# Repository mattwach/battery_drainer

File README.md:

# battery_drainer

This project describes hardware to safely discharge batteries to a user-chosen
level.

# Why?

Before I started flying RC models (many years ago), the concept of managing
batteries was off my radar.  While in the hobby, it became clear that proper
management makes a big difference in how long batteries last and how much power
they will deliver.

Storing lithium ion batteries fully-charged or fully-drained causes them to
degrade permanently.  It's much better to store them in a half-charged state.

Since lithium batteries are used basically everywhere (phones, tools, laptops,
    cars, on and on), being aware of these concepts can help you keep more of
your devices running longer and more healthy.

Many non-lithium batteries have "memory effects" and can benefit from a deep
discharge now and then.  See your particular battery type for details on how to
maintain/restore it.

Other applications for discharging include testing battery capacity and
preparing it for disposal.

# Caution

Following anything written in this document is at-your-own risk.

Batteries are energy storage devices and thus carry an inherent risk.  If you
are not familiar with the battery type you are working with, take a few moments to
educate yourself on recommended handling practices.

When working with an untested unit or new batteries, I suggest extra caution.
For example doing initial testing outside on concrete or in a fire pit.

This design incorporates a protection fuse.  I recommend using the
*smallest-sized fuse* that meets your requirements.  If anything goes wrong
with the firmware, a hardware component, or the hardware build, the fuse will
limit the maximum current that can flow.  Starting with a small fuse and
upgrading it later could be a good verification strategy.

# Pre-existing Market Solutions

If you look up "LIPO Battery Discharger" on Amazon or similar, you will find a
variety of products.  These might work for you but note that the project I am
describing has some advantages over what you can buy:

1. Higher maximum power.  The unit I built is running great at 350W.  The components
   I chose are speced to 460W and 30A.  Since you are building it yourself,
   you can choose a transistor/cooling combo that supports the power dissipation
   you need.
2. Support for "safe" multiboards.  My project has a diode-protected multiboard
   that allows you to safely plug in multiple batteries that are at different 
   discharge levels. This protection requires the discharger account for the 
   voltage drop across the protection diodes, which commercial charges do not
   typically do.
3. Support of 1S packs.  Many chargers have a 2S minimum.
4. Lots of customization.  My project lets you customize voltages and
   create special profiles.  For example, I have one that takes packs down to
   4V/Cell, which is useful for packs that I want ready-to-use in worklights and tools.
5. Detailed status.  The OLED of this project gives lots of information
   during the discharge which can help you guage the health of the pack.
6. Support for more battery types than just LIPO, due to the extensive 
   customization ability.

# Using

## User Interface

The unit has four UI buttons: On, Off, Select and OK.

When the device is initially powered up, it will display the current voltage,
cell count and the target voltage.  It also shows a scrollable list of
profiles to choose from:

The user chooses a profile with "Select" and presses "OK" to start discharging.
During discharge, the following status information is displayed (the ghosting
in the image is because the unit was actively updating during the photo):

Information shown includes:

* Time running
* Number of mAH discharged so far
* Battery voltage and cell count
* Target voltage
* Discharge Current
* Power (Voltage * Current)
* Temperature
* FET power level %
* Fan power level %

If the FET power level is limited < 100%, then the parameter that is limiting
the power is highlighted as inverse text.  In the example above, this limit is
overall power draw.  A lower-cell-count battery might hit the max current
instead.  A small battery might be limited by voltage sag.  A hot day might
introduce a temperature limit.  All limits are user configurable - but you'll
need to be aware of what your built hardware can handle and test higher limits
with due caution.

When the discharge is complete, the unit will show some stats for a configurable
amount of time before automatically shutting down.  Here is an example:

After shutdown, the unit takes very little power (a few microamps) to avoid
further unintended drainage of smaller packs.

## Configuration

Profiles can be edited by connecting a computer to the unit via USB and starting
a terminal program.  On my Linux laptop, I used:

    minicom -b 115200 -P /dev/ttyUSB0

Refer to the [dedicated configuration guide](configuration.md) for details
about how to configure settings, calibrate the device and create/edit profiles.

# Building

## Parts list

To see the parts list, open up the schematic in KiCad and look at the "Symbol
Fields Table".  It looks like a spreadsheet icon in the UI.  Here you will find
a list of parts and links for building an order.  Here is a snapshot of what
the list looked like at some point:

## Schematic Overview

Note that the images below are a snapshot of the schematic and not fully
up-tp-date.  See the KiCad original for the latest design.

Here is the complete design (click to expand):

Here is an early Falstad simulation that gives a basic idea of how the circuit
works:

https://tinyurl.com/2qg4xwyj

There is much going on here.  The sections below break down and explain one
subcircuit at a time.

### Power Dissipation

[Falstad model](https://tinyurl.com/28p9fv3n)

This is a set of 4 P-Channel MOSFETs connected in parallel:

More or less *could* also work.

**Note** The schematic shows four PFETs in parallel.  The unit *I actually
built* uses a single high-power FET instead.  I think that four PFETs would
still work but have not confirmed it.  The main risk of using 4 is that they
will be unevenly loaded to the point where one of them is damaged.  I do
believe that they will be unevenly loaded at lower currents but not after the
current ramps up enough to matter.  Again, I have not confirmed this.  Using a
single high-power FET is my recommendation if you want to play it safer.

The FETs in this design are (unusually) run in their "Ohmic" region which
is controlled by the gate-to-source voltage (Vgs) as exampled in the FQP27P06
datasheet graph below:

### Vgs Control

[Falstad model](https://tinyurl.com/2bj46fut)

To achieve the target Vgs for the FETs, we the following circuit:

The main element here is the 10u capacitor on the right side of the image.
The voltage across this capacitor is the gate voltage that
each FET will see.

Filling the capacitor is the 5k resistor, R16.  If only this resistor and the
capacitor existed, then the RC constant would be 5000 * 10e-6 = 50ms.  When the
capacitor is sufficiently charged, the FETs will be turned off.

The two transistors (Q6, Q9) are used to drain the capacitor.  The one on the
left is a "slow" drain and the one on the right is a "fast" drain.  The size of
the resistors (R17 and R20) determines the drain speed.  A microcontroller
feeds in a PWM to open/close the transistor.  The duty cycle of this PWM
signal determines how much current is pulled on average and the frequency
of this PWM signal determines how smooth/stable the voltage will be.

The reason for two drains (verses one) is to support a larger voltage
range.  At lower voltages (4V), the FAST drain circuit is needed
to get the Vgs lower than the SLOW drain can achieve.  For higher voltages
(25V), the SLOW drain provides better control resolution.  Depending on the
FET you go with and voltage range you want to support, a single drain
may work fine.

In the power-on state, we can assume that SLOW and FAST are not driven at all
(high Z).  In this state the two 50k pulldown resistors (R14, R18) turn off Q6
and Q9 causing the capacitor to fill up and turn off the main power FETs.

The 100K pull down resistor (R25) slowly drains the capacitor so that it at a known
voltage (0V) when the unit is unplugged and idle.

## Inrush protection

[Falstad model](https://tinyurl.com/2y8c54c8)

On initial battery plug-in, the 100ms or so it takes the capacitor (C4) to
charge via R16 could allow a high current to pass through the FETs for that
time period.  This is mitigated by the following inrush protection circuitry:

Fully understanding this block will require studying the full schematic.  A
partial understand can be gained from the image above and the Falstad model.  We
basically have another way to fill the capacitor C4 which is "enabled" when the
battery is plugged in but the user has not pressed the power button yet.  The
way this works is that the source of the FET Q5 is connected to the battery
and the small 10 ohm R13 allows for a rapid fill.  R8 is connected to the
microcontroller power and is thus grounded on plug-in, turning "on" the
FET.

When the user powers on the device (after the battery is plugged in), there is
voltage near-battery going to R8 which turns off the FET and cuts off R13.

### Current Sense 

[Falstad model](https://tinyurl.com/253e6aln)

One of the four ways the microcontroller decides where to set Vgs is by
monitoring the current flowing through the FETs  (the other three are voltage,
power, and temperature).  An ADC within the microcontroller measures the voltage
across the resistors (R22-R24) then uses Ohm's law (I = V/R) to determine the
current.

Resistor values were chosen for a full 3V swing at 30A of current, this allows
us to use the full 12-bits of ADC resolution for good accuracy.  The downside
is that 3V * 30A = 90W, which is a lot for a resistor to dissipate.  To support
this, I chose 3 35W 0.4 ohm resistors connected in parallel for a total dissipation
capability of ~100W and an equivalent resistance of 0.133 ohm.  Potentially
wasting this much power on a current measurement would normally be frowned upon but
in this application it's actually helping take some load off the main power FET.

A Zener diode (U5) is used to protect the ADC of the microcontroller in the
event that the divided voltage is too high (> 3V).  This is a protection
feature that serves no function under "normal" operating conditions.

### Protection Fuse

We also have a protection fuse to help protect against software bugs or other
unexpected problems.  More protection would be offered if the fuse were right at
the battery input but this would introduce a further temperature-dependent
voltage drop that would throw off the voltage measurement.  The "unprotected"
components are the digital logic which should be low current draw barring a
physical issue with the board (< 100 mA)

### Voltage Sense

[Falstad model](https://tinyurl.com/2aavu5hb)

The microcontroller monitors the overall battery voltage to determine a sag
value and to determine when the drain process is completed.

The circuit is a simple voltage divider with a capacitor to help stabilize the
reading.

Sag is determined by periodically turning off the FETs (say for one second every
15 seconds) and measuring the "unloaded" voltage of the pack.  This can then be
used a reference value to determine the sag.

The voltage at R9 is not exactly the battery voltage as it has to pass through a
a diode and FET.  The software provides a calibration value to account for this
drop.

### Temperature Sense

A temperature sensor is placed against the heatsink and as-close-as-possible to
the FET to monitor the FET temperature.  This feedback can be used to control a
cooling fan (described below) and, if this is inadequate, reduce the current draw.

### Power cutoff

[Falstad model](https://tinyurl.com/22wuu5mp)

The battery drainer is designed to draw nearly zero power (outside of parasitic
losses) when it is off, including after the discharging has completed.  Thus the
user can leave the unit unattended (assuming the needed precautions have been
taken) without concern of parasitic drain.

This is implemented with the following circuit:

The Q2 FET is key.  It determines if the microcontroller gets any power.
Q2 is off by default, turned off by R2.  There are two ways to turn it on:

1. If the user presses SW5
2. If the microcontroller activates Q1 via "EN".  The microcontroller does
   this as soon as it can (in a split second) and holds it high until the
   microcontroller decides that it is time to power down OR the user presses
   the "OFF" button which forces Q2 off.

### ADC reference

When using an ADC, one can typically choose from several different sources for
the calibration with the internally-generated 3.3V source as the most
convenient.  The downside of choosing this source is mediocre accuracy.

This design uses the alternate `ADC_VREF` input with a `LM4040` voltage reference
to allow for more accurate measurements.

### OLED connection

The design breaks out an I2C 4 pin header that is typical for an I2C OLED.  A
128x64 design is the intended unit but anything that supports I2C could be
supported with appropriate firmware modifications.

### Fan connection

The battery drainer effectively converts battery energy to heat, thus you'll need
a cooling strategy to avoid overheating and damaging the discharge circuit.
Like cooling other devices such as CPUs and GPUs, a passive solution is
sometimes adequate and an active solution is often needed.

The circuitry below supports a PWM-based fan controller.

The circuit is just a 12V linear regulator with supporting capacitors.  The
connections support "PWM" style PC case fans which generally accept a 25Khz
PWM signal on pin 4.

A flyback diode is needed when powering generic motors but is unlikely to be
needed here as PWM-controlled motors usually already have one in the motor
control circuit.  You can add one for peace-of-mind if you choose.

### PI Pico Microcontroller

As is typical, a microcontroller orchestrates the operation.  Here I chose a PI
Pico because it is inexpensive and quite capable.  It's main downside is the
lack of a low-power sleep mode, but the Power cutoff circuit explained above
compensates for this shortcoming.

A little bit on the tasks the Pico must attend to:

1. When the unit is powered-up, the Pico must raise the EN pin to keep the power  
   active.  It must lower the EN pin when it is time to shutdown.
2. It controls the dissipation rate of the main FETs via PWM signals on the SLOW 
   and FAST pins.
3. It measures current by ADC decoding the voltage at the CUR pin.
4. It measures the battery voltage via an ADC.
5. It provides an output display via SDA and SCL
6. It controls the fan speed (if present) via the FAN pin.
7. It monitors the buttons Select and OK buttons.

## PCB Layout

The PCB layout is above.  Some notes on the layout:

* The dimensions of the board are 122 x 88 mm (4.8 x 3.5 inches)
* Power FETs and resistors are aligned so that a single (large) heatsink can service all of them
* Large traces are used in the higher current areas.
* Large vias are used to try and distribute current and reduce hotspots. 

I went with thicker 2oz copper when manufacturing this board to handle the potentially-large current.

Here are some images of the board, unpopulated and with most components added:

Note that the completed board had a bug where I forgot to add a power-cutoff to
the fan.  If not corrected, this could have caused the fan to draw ~5-10 mA even
after charging is completed.  The fix was to add a PFET (green wires).  The
board design now incorporates the FET on the board.

## Daughterboard

You could plug a single battery into the unit or use a parallel adapter.  Safer
than a parallel adapter would be a board with integrated diodes.  This will
allow batteries of different charge levels to be plugged in without the concern
of large current flows due to unequal discharge levels.  The firmware can
account for the drop across the diodes after the user calibrates the board.  

A bundled example provides connection for 6 XT-60 packs.  Changing the number of
packs or the connector type is of course doable:

# Firmware

If you don't want to build the firmware yourself, there is a prebuilt
version [here](https://github.com/mattwach/battery_drainer/tree/main/firmware).

The firmware, `battery_drainer.uf2` is in a standard PI Pico format.  One
way to download it is to mount the Pico as a USB drive and copy over the file.
Refer to beginner PI Pico tutorials for more information, such as
[this one](https://datasheets.raspberrypi.com/pico/getting-started-with-pico.pdf).

If you do not wish to build the firmware yourself, feel free to skip to the
next section.

The firmware is build using a script that wraps the official pico build
system.  To run it, you execute `bootstrap.sh` which exists in [the src/ directory](https://github.com/mattwach/battery_drainer/tree/main/src).

    ./bootstrap.sh
    cd build
    make -j

Let's take a look inside the file:

```
$ cat bootstrap.sh 
#!/bin/bash

if [ ! -f lib/pico_uart_console/CMakeLists.txt ]; then
  git submodule init
  git submodule update
fi

rm -rf build
mkdir build
cd build
cmake ..
```

All standard git and cmake operations which you can execute individually
if you prefer (or are running in an environment where executing `bootstrap.sh`
directory will not work).

# Case Design

For cooling, I ended up going with [2 120x69x36 mm finned alunimum heatsinks](https://www.amazon.com/gp/product/B07TJY3GKP) which cost me $13 each for a
total of $26.  These work great but having to use two is a bit inconvenient, due
to the vertical seam in the center.  I tapped holes in these heatsinks, both
for mounting the board and for holding the FETs, resistors, and temperature
sensors securely to the heat sink (with the aid of thermal paste to complete
the thermal connection).

On the backside of the heatsink, I have a 120mm fan which blows air into the
fins.  The microcontroller controls fan speed based on current temperature
and power dissipation.

At first everything was held together with wires.  I wan't sure if a 3D printed
solution would be able to tolerate the dissipated heat.  But after experiencing
with the unit and doing official (temperature probe, IR camera) and non official measurements (finger touch), I determined it would probably be ok.

I ended up designing a case using Open SCAD:

Design files are included with the project [here](https://github.com/mattwach/battery_drainer/tree/main/case).  Ready to print models
are [here](https://github.com/mattwach/battery_drainer/tree/main/case/export).

After many uses, the case is holding up fine with no signs of warping.  Note that I used PETG for the case as PLA has a tendency to "creep" over time, even
at slightly elevated temperatures.

The front plate is acrylic.  I used a 3018 CNC machine to cut it out.  Printing
a cover or making something by hand are of course other options,

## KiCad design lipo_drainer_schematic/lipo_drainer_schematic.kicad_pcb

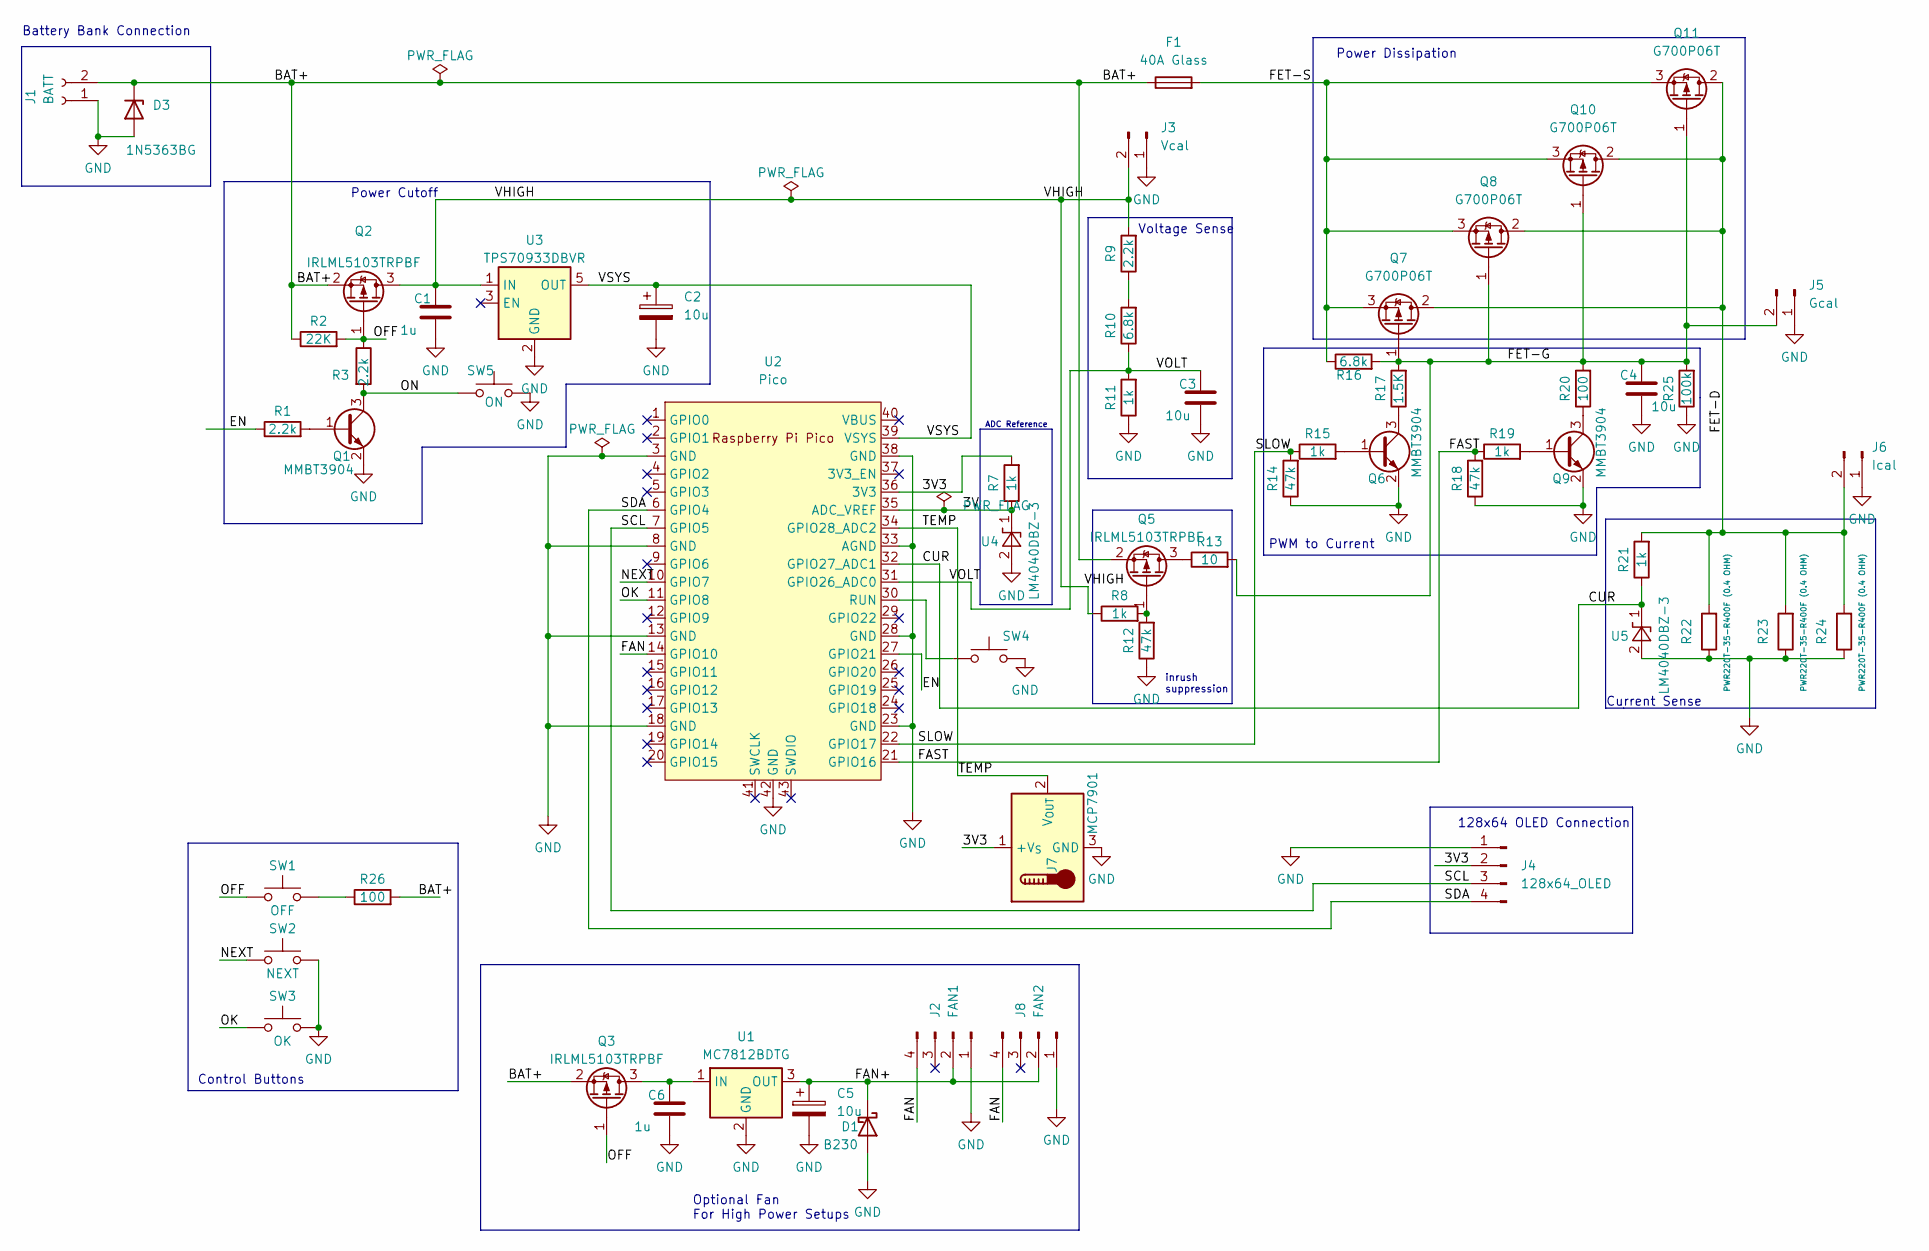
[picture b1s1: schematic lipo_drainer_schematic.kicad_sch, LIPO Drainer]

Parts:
C1, C6: 1u; C_1206_3216Metric_Pad1.33x1.80mm_HandSolder
C2, C3, C4, C5: 10u; C_1206_3216Metric_Pad1.33x1.80mm_HandSolder
D1: B230; D_SMB
D3: 1N5363BG; D_DO-201AD_P15.24mm_Horizontal
F1: 40A Glass; Fuseholder_Clip-6.3x32mm_Littelfuse_102_Inline_P34.21x7.62m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
J1: BATT; AMASS_XT60PW-M_1x02_P7.20mm_Horizontal
J2: FAN1; PinSocket_1x04_P2.54mm_Vertical
J3: Vcal; PinSocket_1x02_P2.54mm_Vertical
J4: 128x64_OLED; OLED_128_64_1.3in
J5: Gcal; PinSocket_1x02_P2.54mm_Vertical
J6: Ical; PinSocket_1x02_P2.54mm_Vertical
J7: MCP7901; TO-92_Inline
J8: FAN2; PinSocket_1x04_P2.54mm_Vertical
Q1, Q6, Q9: MMBT3904; SOT-23
Q2, Q3, Q5: IRLML5103TRPBF; SOT-23
Q7, Q8, Q10, Q11: G700P06T; TO-220-3_Vertical
R1, R3, R9: 2.2k; R_0805_2012Metric_Pad1.20x1.40mm_HandSolder
R2: 22K; R_0805_2012Metric_Pad1.20x1.40mm_HandSolder
R7, R8, R11, R15, R19, R21: 1k; R_0805_2012Metric_Pad1.20x1.40mm_HandSolder
R10, R16: 6.8k; R_0805_2012Metric_Pad1.20x1.40mm_HandSolder
R12, R14, R18: 47k; R_0805_2012Metric_Pad1.20x1.40mm_HandSolder
R13: 10; R_0805_2012Metric_Pad1.20x1.40mm_HandSolder
R17: 1.5K; R_0805_2012Metric_Pad1.20x1.40mm_HandSolder
R20, R26: 100; R_0805_2012Metric_Pad1.20x1.40mm_HandSolder
R22, R23, R24: PWR220T-35-R400F (0.4 OHM); TO-220-2_Vertical
R25: 100k; R_0805_2012Metric_Pad1.20x1.40mm_HandSolder
SW1: OFF; SMD_Button_6mm_3_5mm
SW2: NEXT; SMD_Button_6mm_3_5mm
SW3: OK; SMD_Button_6mm_3_5mm
SW4: RUN; SMD_Button_6mm_3_5mm
SW5: ON; SMD_Button_6mm_3_5mm
U1: MC7812BDTG; TO-252-2
U2: Pico; RPi_Pico_SMD_TH
U3: TPS70933DBVR; SOT-23-5
U4, U5: LM4040DBZ-3; SOT-23

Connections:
/3V: R7.1, U2.35 (ADC_VREF), U4.1 (K)
/3V3: J4.2, J7.1 (+V_{S}), R7.2, U2.36 (3V3)
/BAT+: D3.1 (K), F1.1, J1.2, Q2.2 (S), Q3.2 (S), Q5.2 (S), R2.1, R26.2
/CUR: R21.1, U2.32 (GPIO27_ADC1), U5.1 (K)
/EN: R1.1, U2.27 (GPIO21)
/FAN: J2.4, J8.4, U2.14 (GPIO10)
/FAN+: C5.1, D1.1 (K), J2.2, J8.2, U1.3 (OUT)
/FAST: R18.2, R19.1, U2.21 (GPIO16)
/FET-D: J6.2, Q7.2 (D), Q8.2 (D), Q10.2 (D), Q11.2 (D), R21.2, R22.2, R23.2, R24.2
/FET-G: C4.1, J5.2, Q7.1 (G), Q8.1 (G), Q10.1 (G), Q11.1 (G), R13.2, R16.2, R17.2, R20.2, R25.2
/FET-S: F1.2, Q7.3 (S), Q8.3 (S), Q10.3 (S), Q11.3 (S), R16.1
/NEXT: SW2.1, U2.10 (GPIO7)
/OFF: Q2.1 (G), Q3.1 (G), R2.2, R3.1, SW1.1
/OK: SW3.1, U2.11 (GPIO8)
/ON: Q1.3 (C), R3.2, SW5.1
/SCL: J4.3, U2.7 (GPIO5)
/SDA: J4.4, U2.6 (GPIO4)
/SLOW: R14.2, R15.1, U2.22 (GPIO17)
/TEMP: J7.2 (V_{OUT}), U2.34 (GPIO28_ADC2)
/VHIGH: C1.1, J3.2, Q2.3 (D), R8.1, R9.2, U3.1 (IN)
/VOLT: C3.1, R10.1, R11.2, U2.31 (GPIO26_ADC0)
/VSYS: C2.1, U2.39 (VSYS), U3.5 (OUT)
GND: C1.2, C2.2, C3.2, C4.2, C5.2, C6.2, D1.2 (A), D3.2 (A), J1.1, J2.1, J3.1, J4.1, J5.1, J6.1, J7.3 (GND), J8.1, Q1.2 (E), Q6.2 (E), Q9.2 (E), R11.1, R12.1, R14.1, R18.1, R22.1, R23.1, R24.1, R25.1, SW2.2, SW3.2, SW4.2, SW5.2, U1.2 (GND), U2.3 (GND), U2.8 (GND), U2.13 (GND), U2.18 (GND), U2.23 (GND), U2.28 (GND), U2.33 (AGND), U2.38 (GND), U2.42 (GND), U3.2 (GND), U4.2 (A), U5.2 (A)
unnamed: Q1.1 (B), R1.2
unnamed: C6.1, Q3.3 (D), U1.1 (IN)
unnamed: Q5.3 (D), R13.1
unnamed: Q5.1 (G), R8.2, R12.2
unnamed: Q6.1 (B), R15.2
unnamed: Q6.3 (C), R17.1
unnamed: Q9.1 (B), R19.2
unnamed: Q9.3 (C), R20.1
unnamed: R9.1, R10.2
unnamed: R26.1, SW1.2
unnamed: SW4.1, U2.30 (RUN)

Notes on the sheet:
inrush suppression
Battery Bank Connection
Control Buttons
Power Dissipation
Optional Fan For High Power Setups
Current Sense
ADC Reference
Voltage Sense
PWM to Current
Power Cutoff
128x64 OLED Connection

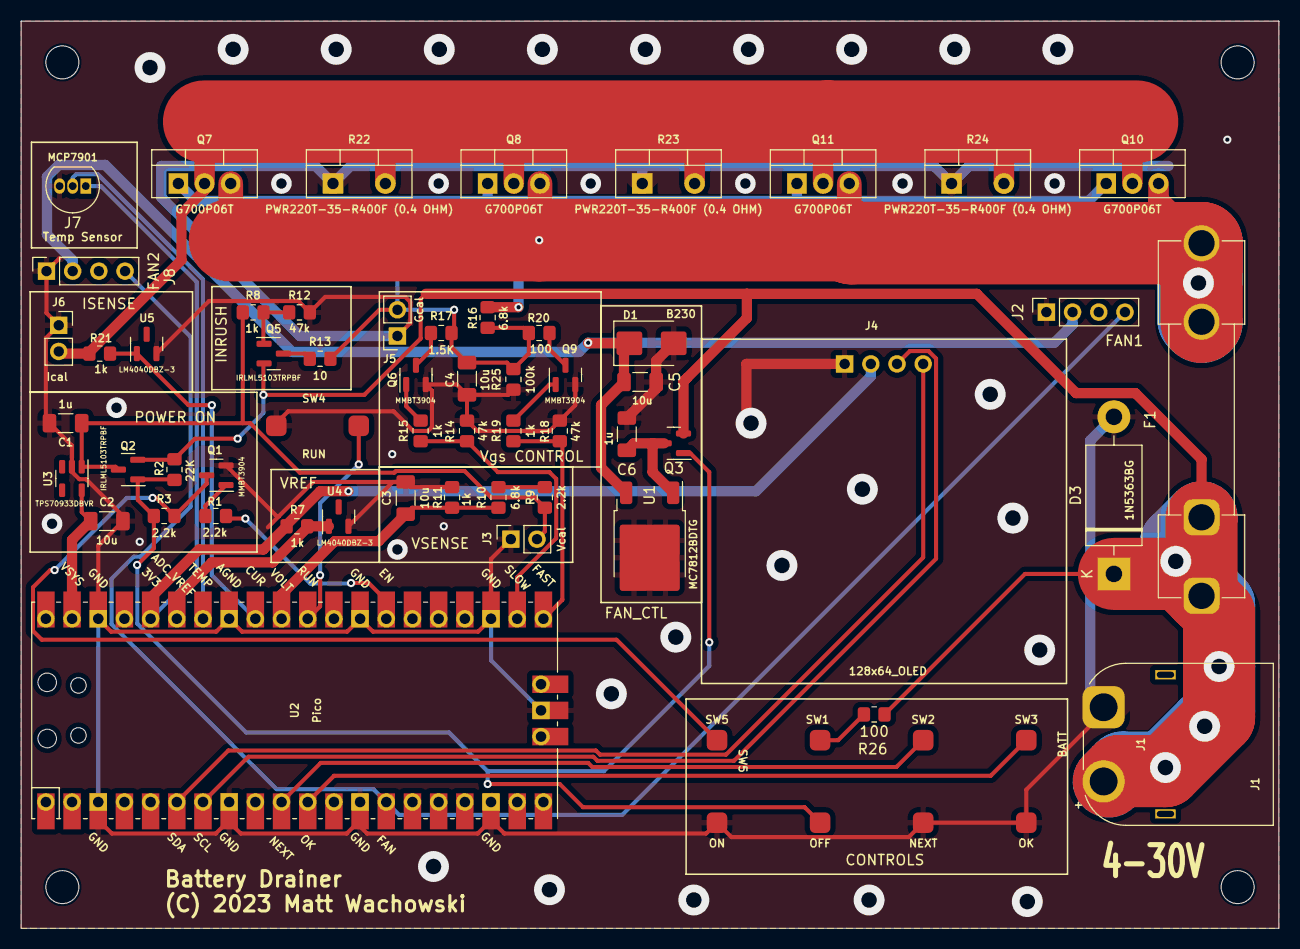
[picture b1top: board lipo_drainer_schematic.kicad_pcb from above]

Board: 2 copper layers, 122.0 x 88.0 mm, 64 parts (0 on the bottom side), 34 nets.

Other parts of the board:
NEHOLE: MountingHole_3.2mm_M3
NWHOLE: MountingHole_3.2mm_M3
SEHOLE: MountingHole_3.2mm_M3
SWHOLE: MountingHole_3.2mm_M3

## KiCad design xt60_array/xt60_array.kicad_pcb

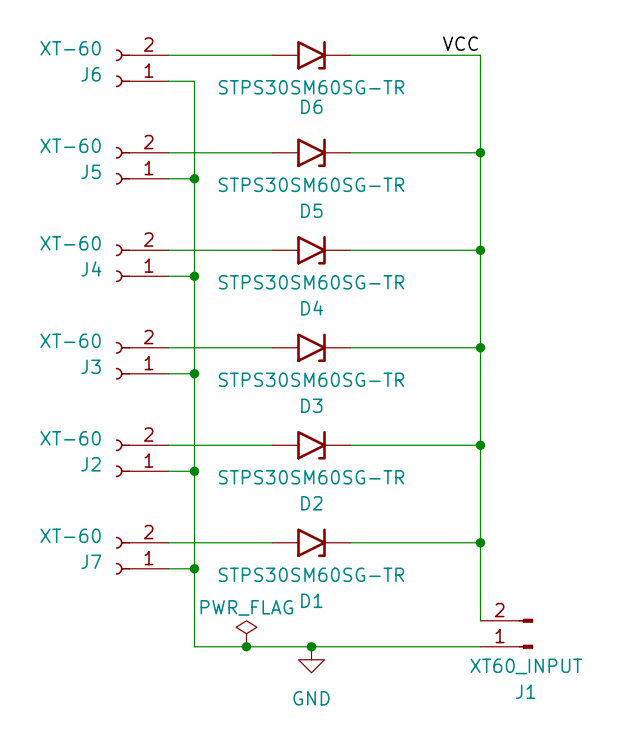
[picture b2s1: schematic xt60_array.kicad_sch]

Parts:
D1, D2, D3, D4, D5, D6: STPS30SM60SG-TR; TO-263-2_TabPin1_Alt
J1: XT60_INPUT; AMASS_XT60PW-F_1x02_P7.20mm_Horizontal
J2, J3, J4, J5, J6, J7: XT-60; AMASS_XT60-M_1x02_P7.20mm_Vertical

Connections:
/VCC: D1.1 (A1), D2.1 (A1), D3.1 (A1), D4.1 (A1), D5.1 (A1), D6.1 (A1), J1.2
GND: J1.1, J2.1, J3.1, J4.1, J5.1, J6.1, J7.1
unnamed: D1.2 (A2), J7.2
unnamed: D2.2 (A2), J2.2
unnamed: D3.2 (A2), J3.2
unnamed: D4.2 (A2), J4.2
unnamed: D5.2 (A2), J5.2
unnamed: D6.2 (A2), J6.2

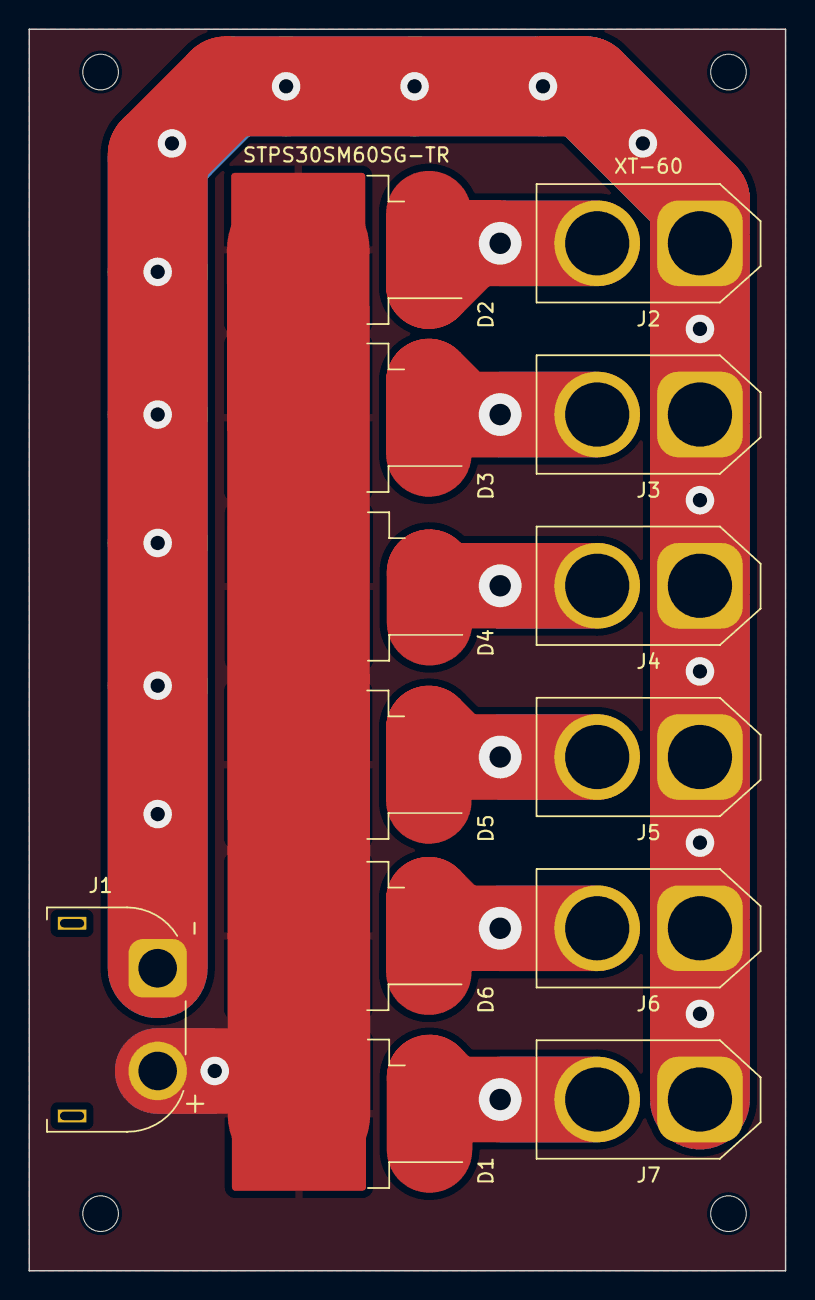
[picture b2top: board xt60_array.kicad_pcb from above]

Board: 2 copper layers, 53.0 x 87.0 mm, 17 parts (0 on the bottom side), 8 nets.

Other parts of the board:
REF1, REF2, REF3, REF4: MountingHole_2.5mm

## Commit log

2023-02-16 Started schematic
2023-02-27 Updated power circuit
2023-03-04 Enhanced schematic, but I'm probably not going with bulbs anymore
2023-03-04 Changed design to use PFETs
2023-03-05 Worked on calibration thoughts.
2023-03-05 Tweaked transistor in power design
2023-03-07 Added inrush current supression.
2023-03-07 Added fan controller
2023-03-07 Added flyback diode to fan control
2023-03-07 Switched fan control regulator to one with an enable pin.
2023-03-28 Changed transistor for less individual parts
2023-03-30 Added documenation for schematic.
2023-03-31 Adding more to the README
2023-04-01 more README work
2023-04-01 Fixed ERC warnings
2023-04-01 Added parts list
2023-04-01 Removed ineffective ON button
2023-04-01 README small fixes
2023-04-01 redo unintended kicad change
2023-04-02 Started work on layout
2023-04-02 Added temperature sensor
2023-04-02 Added more net labels
2023-04-02 Added OLED footprint
2023-04-02 Change XT-60 connecter
2023-04-03 Starting to group PCB layout into logical sections.
2023-04-03 Changed button definitions.
2023-04-03 Placed subblocks in PCB
2023-04-03 Routed and added mounting holes.
2023-04-03 added filled zones
2023-04-03 Label cleanup
2023-04-04 Cleaned up almost all DRC warnings
2023-04-04 Added vias
2023-04-04 Changed OFF button to be directly connected to the FET
2023-04-05 Made Pico PCB labeloing specific
2023-04-05 Added Zener inductance protection.
2023-04-06 Enlarge power vias, update schematic
2023-04-07 Big README update to cover design changes
2023-04-07 Updated falstad models
2023-04-09 Added motor BJT pulldown and redid ground planes
2023-04-11 Changed fan to PWMs
2023-04-11 Updated fuse holder
2023-04-14 Updated PCB layout
2023-04-15 Start of array
2023-04-16 Finished schematic
2023-04-16 Added xt60 daughterboard
2023-04-16 Missed some files on the last commit
2023-04-21 Added gerber exports
2023-04-21 Added gerber export for xt60 array.
2023-04-26 Started PI Pico framework, added oled test.
    It compiles but not yet tested on hardware.
2023-04-27 Added start of vgs_control test (just a console at the moment).
2023-04-27 Draft of vgs_control code.
    I didn't test it if would compile which means that it probably does not.
2023-04-27 Fixes a couple of compile warmings.
    Amazingly, it compiled on the first try, but with a couple warnings.
2023-04-27 Updated console arg counts.
2023-04-27 Fixed get_num uint32 cast
2023-04-27 Added test for vsense.
2023-04-28 vgs_control is now working.
    The main bug was feeding the wrong value into the slice calculation.
    I changed slice to be hard-coded since it's not going to change in
    the hardware anyway.
2023-04-28 Starting fan control as a direct copy of vgs_control.
2023-04-28 Implement changes needed for fan control.
    Mostly just simplification.
2023-04-28 allow for negative vdrop value
2023-04-29 Added some UI to readme
2023-04-29 UI updates in README
2023-04-30 Added settings.h
2023-04-30 Implemented settings and added basic framework for firmware.
2023-05-01 Started Console settings UI.
2023-05-01 Added CNC job for solder paste stencil
2023-05-01 Added stencil for xt60 array
2023-05-02 Added SharedState concept.
2023-05-02 Added OLED and Text initialization.
2023-05-02 Added button sensing.
2023-05-02 Started profile_selection
2023-05-02 Added current_profile render to profile_selection.c
2023-05-03 Update connection message which I already did on some PC.
2023-05-03 Added button controls to profile_selection
2023-05-04 Fixed USB output. Added heartbeat LED.
2023-05-04 Added missing button interrupt handler
2023-05-04 Fix trailing null in text output
2023-05-04 Added ical console command
2023-05-04 Pass current_mv in from main.
    console.g also needs the value.
2023-05-04 Added vcal console command.
2023-05-04 added vsag commands
2023-05-04 Added fan settings to console.
2023-05-04 Fix fan % formatting
2023-05-04 Updated vcal calculation
2023-05-04 Fixed maximum error value reporting
2023-05-04 Fixed some console settings bugs.
2023-05-04 Fixed up flash save
    * Use dynamic addresses based on sizeof(Settings), even though it's
    currentl not needed
    * disable interrupts to avoid a hang
2023-05-04 Added finish_display console command
2023-05-04 Added slew console commands.
2023-05-04 Added new and duplicate console commands
2023-05-05 Added name console command
2023-05-05 Added delete console command
2023-05-05 Added move console command
2023-05-05 Added list console command
2023-05-05 Added vdrop console command.
2023-05-05 Added per_cell_target_volts console command.
2023-05-05 Added per_cell_damage_volts console command.
2023-05-05 Added max_amps console command
2023-05-05 Put in profile index adjustment to handle delete and reloads
2023-05-05 Added per_cell_max_vsag
2023-05-05 Added max_celsius command
2023-05-05 Added max_watts command
2023-05-05 Fixed move dest size calculation
2023-05-05 put in checks for target_mv vs cell count
2023-05-05 Fill in bottom line with space when profile count is low
2023-05-05 Added enable call
2023-05-05 Created utl.h
2023-05-05 Added status message.
2023-05-05 Created power.h
2023-05-06 Started UI for draining battery.
2023-05-06 Fixed header function name typo
2023-05-06 Adds a 50ms startup delay.
    This will allow the OLED to get power and make sure that the EN low
    turn off doesn't lead to a reset -> EN high again (did not confirm this
    happens but it can in theory).
2023-05-06 Added voltage_sense module
2023-05-06 Added logic to account for OLED update time in sleep time.
2023-05-06 Made draining timer functional.
2023-05-06 started implementing final stats
2023-05-06 Changed defaults to correspond with measured values
2023-05-06 Added finished module
2023-05-06 Added damage_warning module
2023-05-06 Added current_sense module
2023-05-06 Added temperature_sensee module
2023-05-06 Added charge_mah calculations
2023-05-06 Added vgs_control module.
2023-05-07 Changed the response tuning model.
2023-05-07 Added fan_control module
2023-05-07 Added fan control logic. Started conversion of vgs control.
2023-05-07 Implemented vgs_control
    This led to a pretty large refactor where DisplayUI parameters were dropped.
    The code will need to be reviewed and tested to find regressions.
2023-05-07 Added more message dialogs
2023-05-07 Added fake_mv command
2023-05-07 Added vsag estimation logic.
2023-05-07 voltage sampling bug fixes
2023-05-11 Increase test vgs program frequency
2023-05-11 Changed SH1106 hardware configuration to rotate the screen 180 degrees
2023-05-11 Added power-sensed fan control
2023-05-12 Unrotate screen. Add fan power to profile output.
2023-05-12 Adds code to stop discharge after target voltage is reached.
2023-05-12 Trims back target voltage a bit when doing the cell calculation.
2023-05-12 Changed limit logic to hold the field inverted for 0.5 seconds.
2023-05-12 Changed top line to show mAh
2023-05-12 Changed UI logic to better show low FET percents.
2023-05-13 Changed fan control to be more gradual.
2023-05-13 Using a 8 sample moving average on current.
    Instantaneous current is a bit hard to work with, due to tuning difficulties of the FET.
2023-05-13 Revert "Using a 8 sample moving average on current."
    The update latency is making the tuning algorithm too unstable.
    This reverts commit 16eb5d84d4965ffdcd41e92defc5fa7b1cbc47c5.
2023-05-13 fixed mah display
2023-05-13 Fixed regression where unloaded voltage samples no longer disabled PWM.
2023-05-13 Do not return early on disable PWM.
    It sometimes leaves the channel locked high!
2023-05-13 Fixed typing bug that caused fet % to be mis displayed.
2023-05-13 Fixed issue where PWM that does not change does not get turned back on after a recal.
2023-05-13 Tryout out average power for fan control
2023-05-13 Tried to make the terminology a bit more consistent
2023-05-13 Fixed command name
2023-05-13 added vscode settings
2023-05-13 Fixed arg count bug
2023-05-13 Removed the word LIPO from the readme where it made sense
2023-05-13 Removed lipo_ prefix from build files
2023-05-13 Always set PWM level and don't disable fan.
2023-05-13 Fixed overflow that would occur if the power/temp were way beyond the upper specified fan limit
2023-05-13 typo fix
2023-05-13 Added build .uf2 files
2023-06-02 Starting 3D case model.
2023-06-02 Added main board and pico.
2023-06-02 Added oled screen to pcb
2023-06-03 Added xt60 connector to main pcb
2023-06-03 Added buttons to main pcb.
2023-06-03 added fuse to main pcb
2023-06-05 Added fan
2023-06-05 Added core include, which NopSCADlibn seems to need.
2023-06-05 Placed fan connector
2023-06-05 Started work on case.
2023-06-05 Added a fan shroud.
2023-06-05 Added Heat sink mount
2023-06-05 Made gaps in fan shroud for wiring
2023-06-05 Made the overall width based on the heat sink mount.
2023-06-05 renamed case to backside
2023-06-05 reduce case_bottom_pad
2023-06-05 Added frontside mounting holes/
2023-06-05 added frontside feet
2023-06-06 added main plate
2023-06-06 Added frontside mounting holes
2023-06-06 Added front plate posts
2023-06-06 Added holeds to posts
2023-06-06 added front feet
2023-06-06 added back feet
2023-06-06 Added hole for fan cable.
2023-06-06 Added glass plate
2023-06-06 Made reset/boot holes smaller
2023-06-06 Added bolts
2023-06-06 Make the openscad library stand-alone
2023-06-06 Changed cable mounting offset to account for an angled connection
2023-06-07 Added glass plate projection
2023-06-10 Changed fron thickness based on real dimensions. Removed fron foot gap
2023-06-10 Added case model exports.
2023-06-11 Added front plate cnc exports
2023-06-20 Stated updating to reflect curent state
2023-06-20 Pulled in these changes
2023-06-22 Moved configuration into a separate doc
2023-06-22 More README updates.
2023-06-27 Added images
2023-06-28 README updates
2023-07-01 Added images for unpopulated and completed boards
2023-07-01 Updated schematic to include FAN FET
2023-07-09 README spelling and formatting fixes.
2023-07-10 More README cleanup
2023-07-14 Added notes on csae design and building firmware.
2023-07-18 Added more to safety section

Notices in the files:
lipo_drainer_schematic/lipo_drainer_schematic.kicad_pcb:
(C) 2023 Matt Wachowski
